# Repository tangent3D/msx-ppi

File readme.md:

### MSX-PPI
MSX-PPI is an MSX compatible programmable I/O cartridge design based around the i8255 Programmable Peripheral Interface (PPI) offering the user 24 I/O pins (as three 8-bit ports) through the MSX cartridge slot.

### Thanks
[@skiselev](https://github.com/skiselev) for his advice  
[xrrawva](http://xrrawva.com/ "xrrawva") for bat graphics and support  
[@apoloval](https://github.com/apoloval) for MSX EEPROM cartridge PCB (used for 02x25 cartridge pins)  
Atsushi Seki. "[Putting Together a Standard Interface Board](https://archive.org/stream/MSX_Magazine_1990-07_ASCII_JP#page/n127/mode/1up "Putting Together a Standard Interface Board")" *MSX Magazine*, Jul. 1990, pp. 128-131.  

### Disclaimer
This is my first PCB design and may contain errors. Please do not hold me responsible for any damage to your system.

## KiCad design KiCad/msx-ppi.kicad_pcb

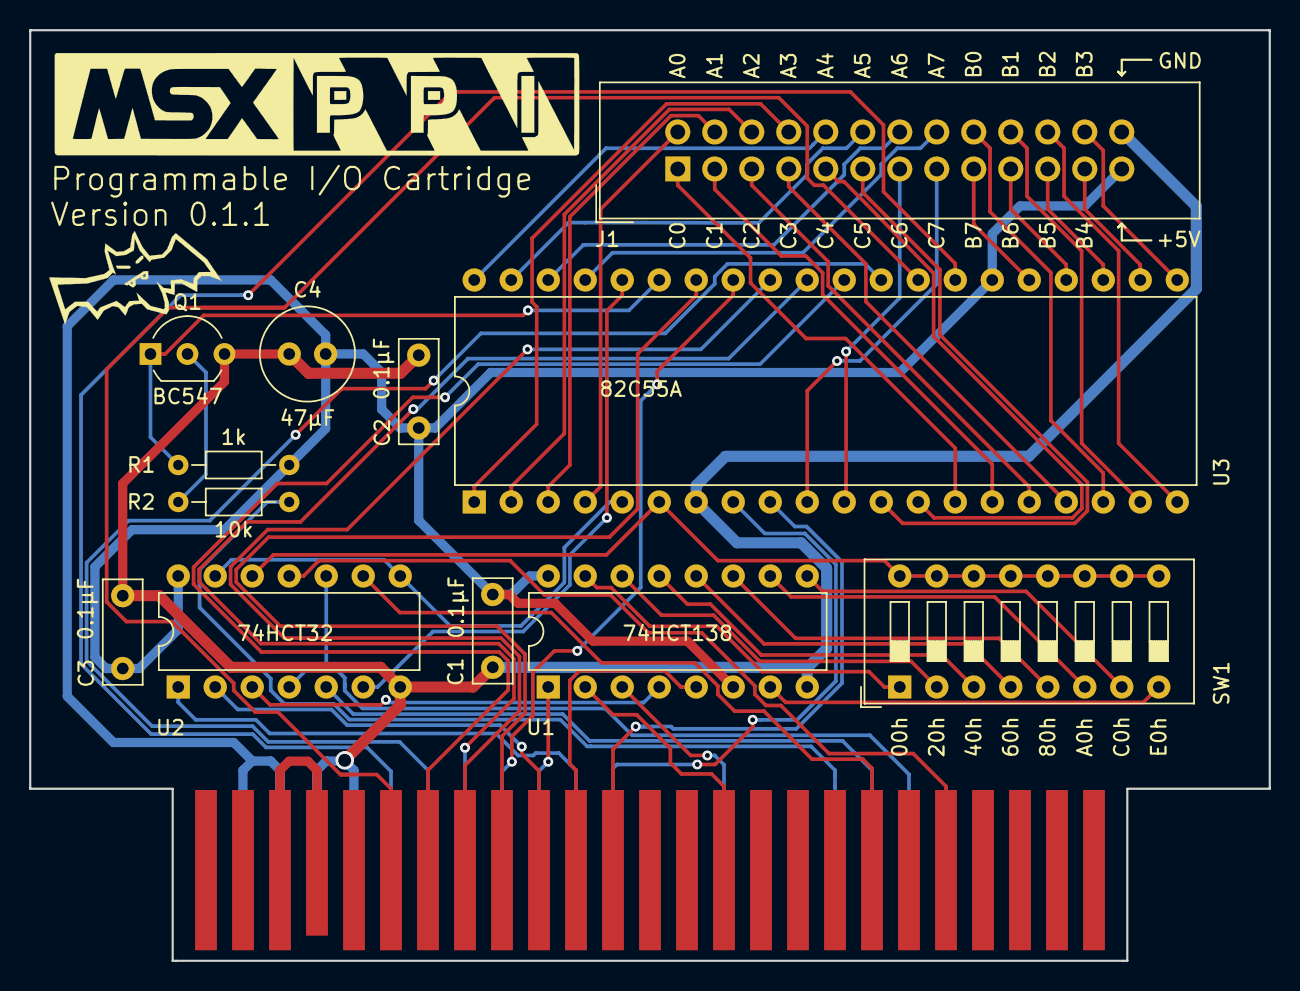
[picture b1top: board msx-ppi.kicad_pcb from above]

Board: 2 copper layers, 85.1 x 63.9 mm, 16 parts (1 on the bottom side), 62 nets.

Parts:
Bat: LOGO; lolbat
C1, C2, C3: 0.1μF; C_Disc_D7.0mm_W2.5mm_P5.00mm
C4: 47μF; C_Radial_D6.3mm_H11.0mm_P2.50mm
J1: Conn_02x13_Odd_Even; IDC-Header_2x13_P2.54mm_Vertical
Logo: LOGO; msx-ppi_logo_F.SilkS_1.425in
P1: CONN_02X25; msx_cartridge
Q1: BC547; TO-92_Inline_Wide
R1: 10k; R_Axial_DIN0204_L3.6mm_D1.6mm_P7.62mm_Horizontal
R2: 1k; R_Axial_DIN0204_L3.6mm_D1.6mm_P7.62mm_Horizontal
SW1: DIPx8; SW_DIP_SPSTx08_Slide_9.78x22.5mm_W7.62mm_P2.54mm
Tangent: LOGO; tangent_0.5in
U1: 74HCT138; DIP-16_W7.62mm
U2: 74HCT32; DIP-14_W7.62mm
U3: 82C55A; DIP-40_W15.24mm

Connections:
A0: P1.28, U3.9
A1: P1.27, U3.8
A2: P1.30, U1.5
A3: P1.29, U2.1
A4: P1.32, U2.2
A5: P1.31, U1.1
A6: P1.22, U1.2
A7: P1.21, U1.3
D0: P1.34, U3.34
D1: P1.33, U3.33
D2: P1.36, U3.32
D3: P1.35, U3.31
D4: P1.38, U3.30
D5: P1.37, U3.29
D6: P1.40, U3.28
D7: P1.39, U3.27
GND: C1.2, C2.2, C3.2, C4.1, J1.26, P1.41, P1.43, Q1.3, U1.8, U2.7, U3.7
unnamed: P1.44, P1.46
unnamed: Q1.1, R2.2, U3.35
unnamed: Q1.2, R1.1
unnamed: SW1.1, U1.15
unnamed: SW1.2, U1.14
unnamed: SW1.3, U1.13
unnamed: SW1.4, U1.12
unnamed: SW1.5, U1.11
unnamed: SW1.6, U1.10
unnamed: SW1.7, U1.9
unnamed: SW1.8, U1.7
unnamed: SW1.9, SW1.10, SW1.11, SW1.12, SW1.13, SW1.14, SW1.15, SW1.16, U2.12, U3.6
unnamed: U1.4, U2.3
unnamed: U2.6, U3.36
unnamed: U2.8, U2.13, U3.5
PA0: J1.2, U3.4
PA1: J1.4, U3.3
PA2: J1.6, U3.2
PA3: J1.8, U3.1
PA4: J1.10, U3.40
PA5: J1.12, U3.39
PA6: J1.14, U3.38
PA7: J1.16, U3.37
PB0: J1.18, U3.18
PB1: J1.20, U3.19
PB2: J1.22, U3.20
PB3: J1.24, U3.21
PB4: J1.23, U3.22
PB5: J1.21, U3.23
PB6: J1.19, U3.24
PB7: J1.17, U3.25
PC0: J1.1, U3.14
PC1: J1.3, U3.15
PC2: J1.5, U3.16
PC3: J1.7, U3.17
PC4: J1.9, U3.13
PC5: J1.11, U3.12
PC6: J1.13, U3.11
PC7: J1.15, U3.10
VCC: C1.1, C2.1, C3.1, C4.2, J1.25, P1.45, P1.47, R2.1, U1.6, U1.16, U2.14, U3.26
\BUSDIR: P1.10, U2.11
\IORQ: P1.11, U2.4, U2.10
\RD: P1.14, U2.9
\RESET: P1.15, R1.2
\WR: P1.13, U2.5

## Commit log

2020-07-02 Added project files
2020-07-04 Changed Q1 footprint
2020-07-04 Fixed path to project footprints
2020-07-17 Changed R2 value to 10k (was 1k)
